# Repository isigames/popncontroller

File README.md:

# popncontroller
Custom made USB-C pop n' music controller

## Why this project?
As someone with some experience in electronics and 3D modeling, I wanted something that was a bit challenging than usual, yet still simple enough to be done in the span of a week.
I also love obscure arcade rhythm games, although I did learn how to use professional design tools the goal of this project was to have fun and utilize my creativity!

## Materials

- 1x XIAO RP2040
- 9x Cherry MX Switches
- 4x M3x16 Bolt
- 4x M3 Heatset
- 1x pop n controller base.step
- 1x pop n controller top.step
- 9x pop n keycap.step
-The pin connectors appear in the 3d model, but they are not needed. Instead, 18 cables need to be soldered to each of the buttons in order for them to be placed. I already have access to the cables.

## Final result
This is how the controller parts will be assembled, note that the cherry switches are not present in this illustration. The grey squares are the PCB components

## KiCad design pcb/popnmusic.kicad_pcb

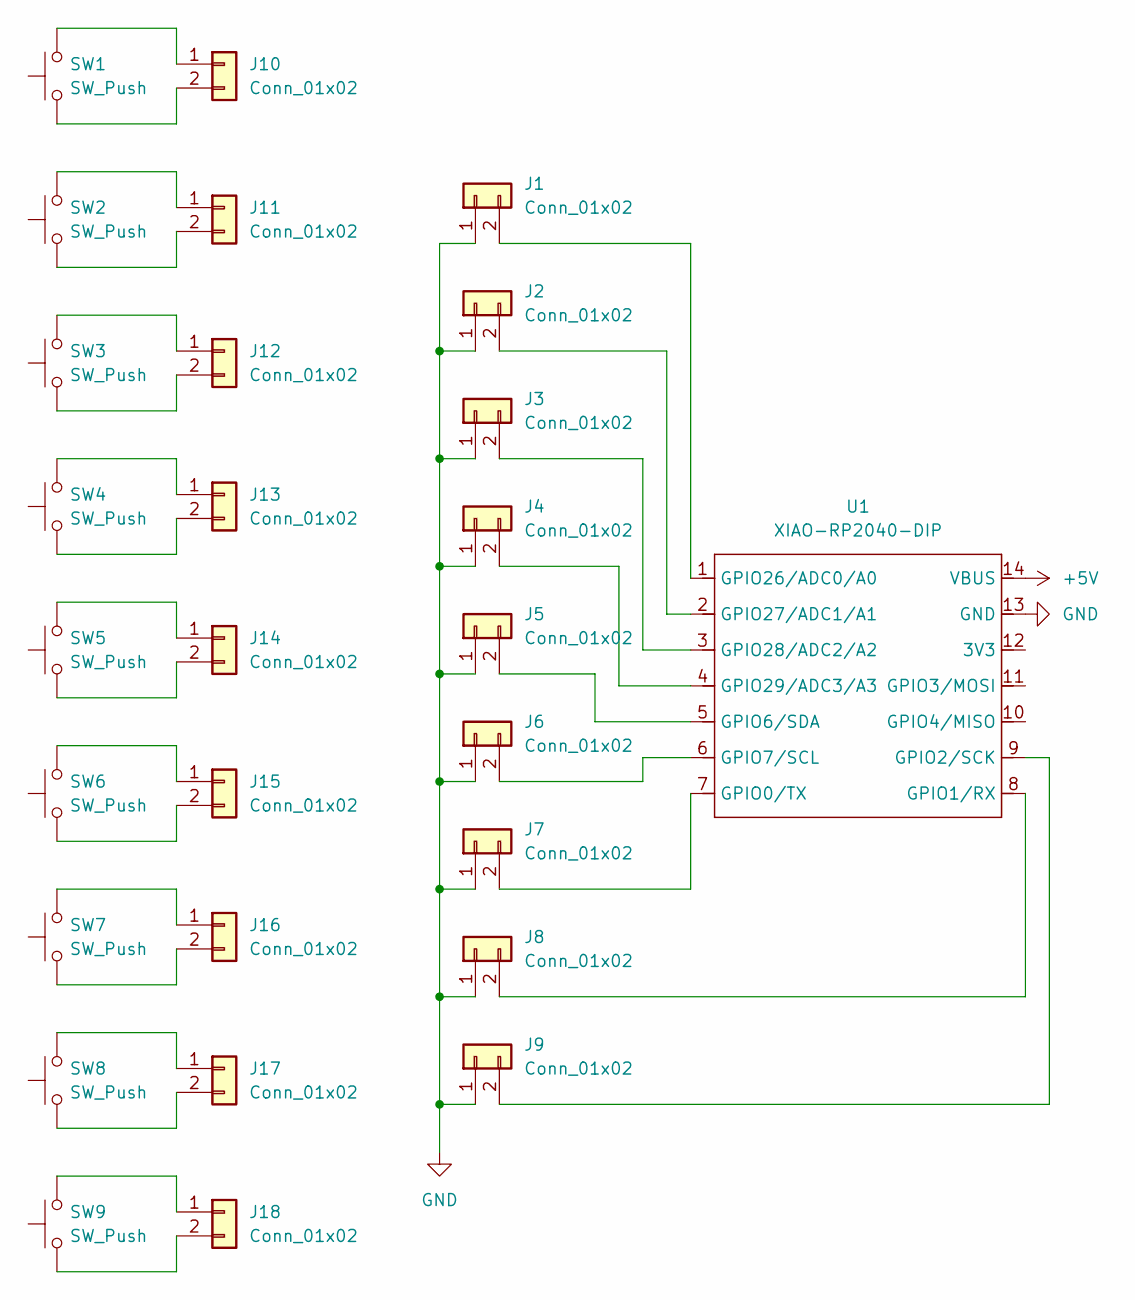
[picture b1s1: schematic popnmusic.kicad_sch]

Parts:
J1, J2, J3, J4, J5, J6, J7, J8, J9, J10, J11, J12, J13, J14, J15, J16, J17, J18: Conn_01x02; PinHeader_1x02_P2.54mm_Vertical
SW1, SW2, SW3, SW4, SW5, SW6, SW7, SW8, SW9: SW_Push; SW_Cherry_MX_1.00u_PCB
U1: XIAO-RP2040-DIP

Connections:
+5V: U1.14 (VBUS)
GND: J1.1, J2.1, J3.1, J4.1, J5.1, J6.1, J7.1, J8.1, J9.1, U1.13 (GND)
unnamed: J1.2, U1.1 (GPIO26/ADC0/A0)
unnamed: J2.2, U1.2 (GPIO27/ADC1/A1)
unnamed: J3.2, U1.3 (GPIO28/ADC2/A2)
unnamed: J4.2, U1.4 (GPIO29/ADC3/A3)
unnamed: J5.2, U1.5 (GPIO6/SDA)
unnamed: J6.2, U1.6 (GPIO7/SCL)
unnamed: J7.2, U1.7 (GPIO0/TX)
unnamed: J8.2, U1.8 (GPIO1/RX)
unnamed: J9.2, U1.9 (GPIO2/SCK)
unnamed: J10.1, SW1.2
unnamed: J10.2, SW1.1
unnamed: J11.1, SW2.2
unnamed: J11.2, SW2.1
unnamed: J12.1, SW3.2
unnamed: J12.2, SW3.1
unnamed: J13.1, SW4.2
unnamed: J13.2, SW4.1
unnamed: J14.1, SW5.2
unnamed: J14.2, SW5.1
unnamed: J15.1, SW6.2
unnamed: J15.2, SW6.1
unnamed: J16.1, SW7.2
unnamed: J16.2, SW7.1
unnamed: J17.1, SW8.2
unnamed: J17.2, SW8.1
unnamed: J18.1, SW9.2
unnamed: J18.2, SW9.1

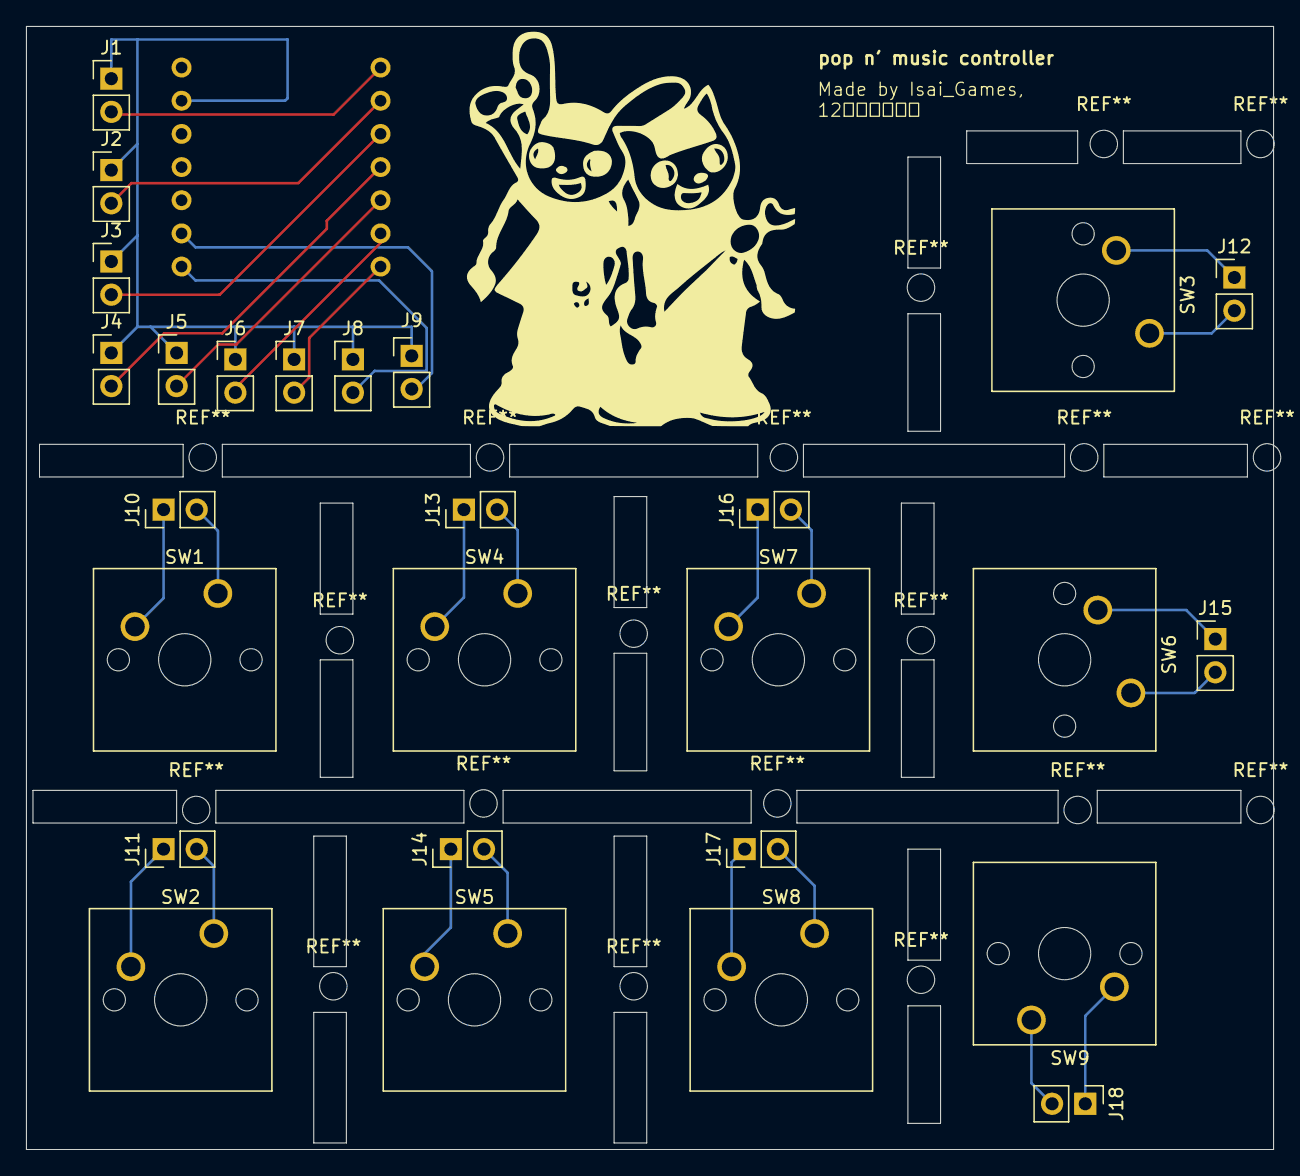
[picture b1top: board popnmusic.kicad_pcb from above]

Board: 2 copper layers, 95.5 x 86.0 mm, 28 parts (1 on the bottom side), 28 nets.

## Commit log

2025-12-23 Create a
2025-12-23 Update a
2025-12-24 Rename controller.py to main.py
